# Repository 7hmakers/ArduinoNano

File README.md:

# ArduinoNano
A Development Board based on ATMEGA328P, compatible with Arduino Nano

Made for FZYZ 7HMakers Club

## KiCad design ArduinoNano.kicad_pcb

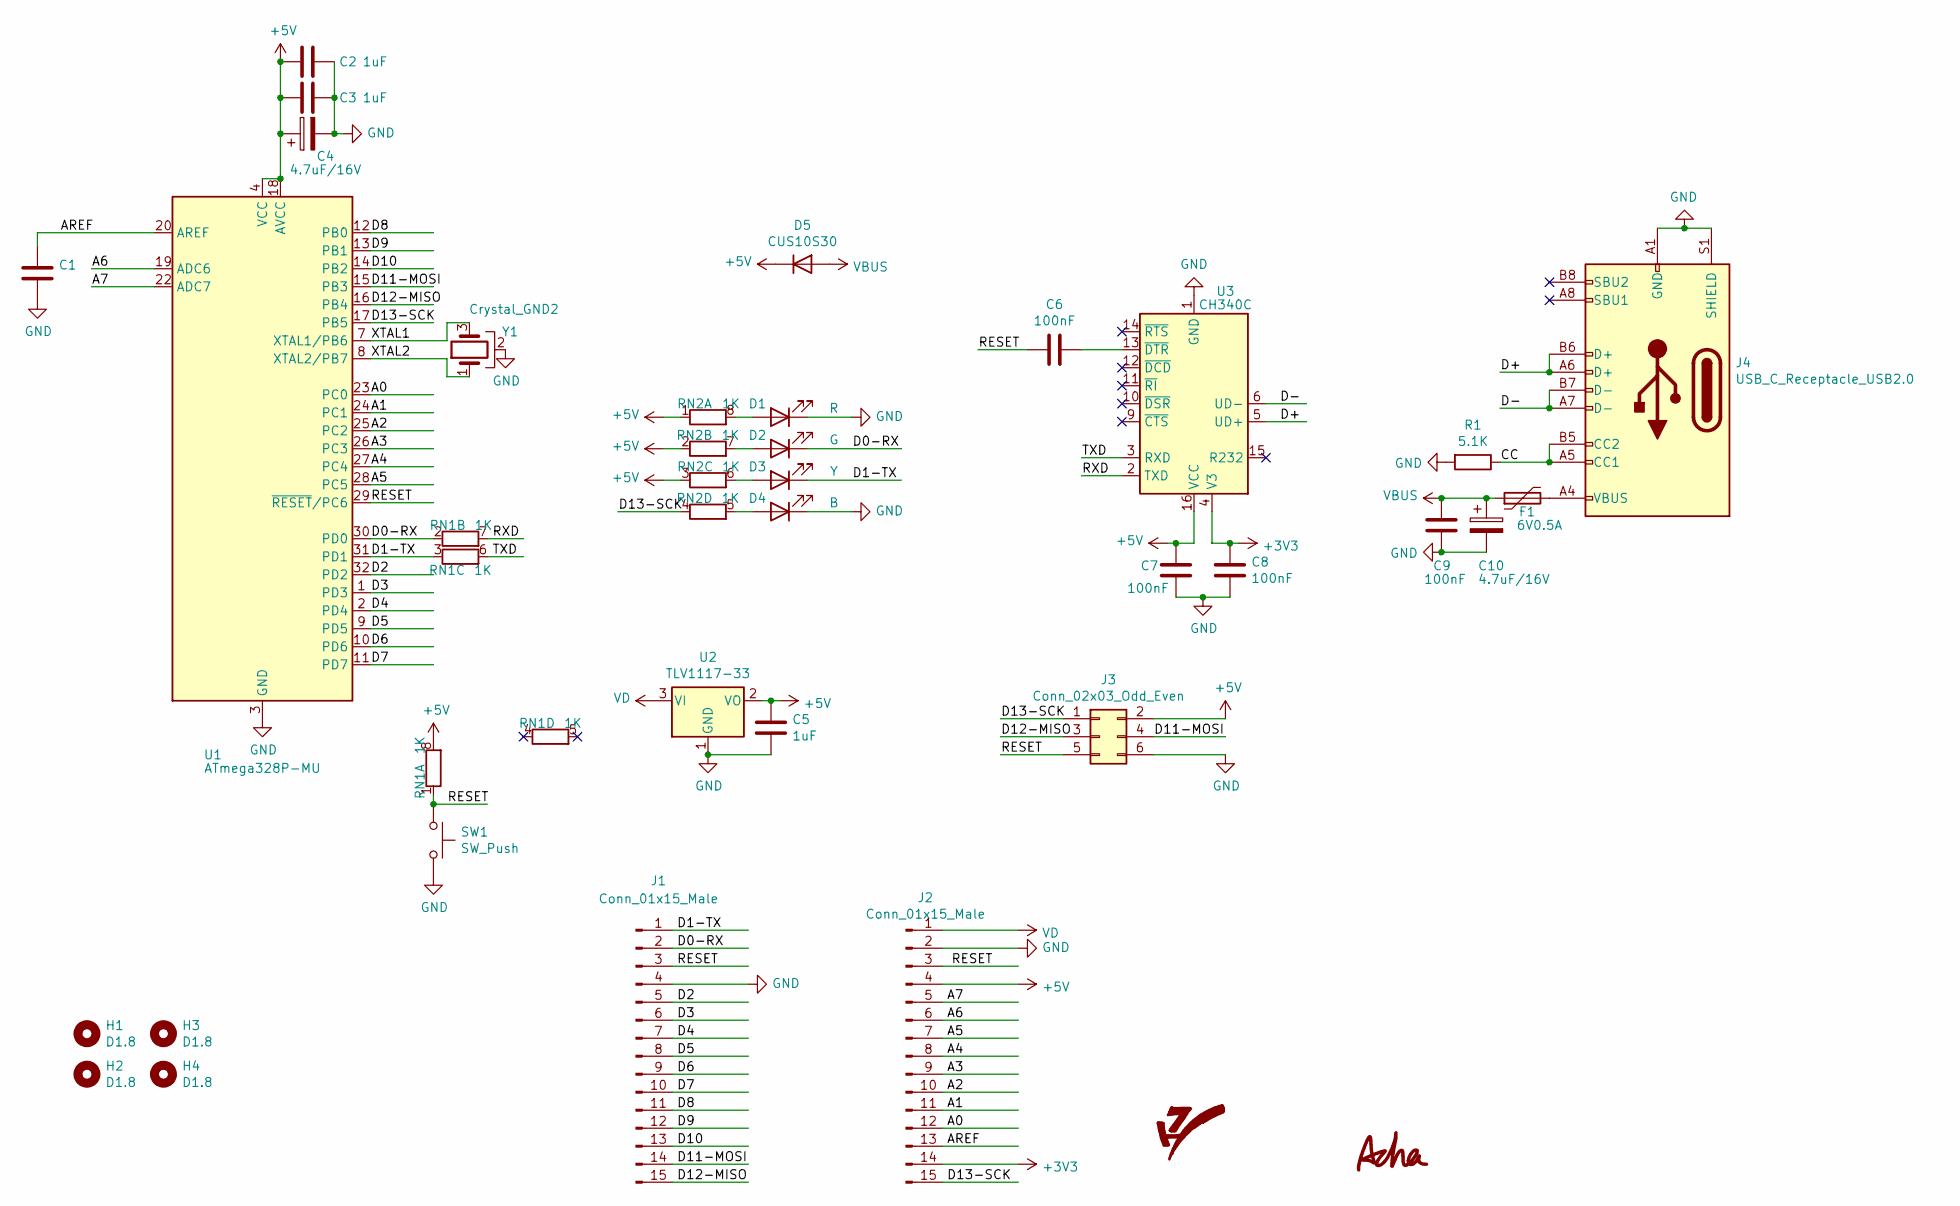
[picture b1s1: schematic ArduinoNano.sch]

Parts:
C1, C6, C7, C8, C9: 100nF; C_0603_1608Metric
C2, C3, C5: 1uF; C_0603_1608Metric
C4, C10: 4.7uF/16V; CP_EIA-3216-18_Kemet-A
D1: R; LED_0603_1608Metric
D2: G; LED_0603_1608Metric
D3: Y; LED_0603_1608Metric
D4: B; LED_0603_1608Metric
D5: CUS10S30; D_SOD-323
F1: 6V0.5A; Fuse_0603_1608Metric
G1: 7Maker_LOGO_SCH_10.8x10.8; 7Maker_LOGO_9.6x9.6
G2: LOGO; Acha_LOGO_5.2x3
H1, H2, H3, H4: D1.8; MountingHole_1.8mm
J1, J2: Conn_01x15_Male; PinHeader_1x15_P2.54mm_Vertical_ard
J3: Conn_02x03_Odd_Even; PinHeader_2x03_P2.54mm_Vertical
J4: USB_C_Receptacle_USB2.0; USB_C_Receptacle_XKB_U262-16XN-4BVC11
R1: 5.1K; R_0603_1608Metric
RN1, RN2: 1K; R_Array_Convex_4x0603
SW1: SW_Push; SW_Push_SPST_NO_Alps_SKRK
U1: ATmega328P-MU; QFN-32-1EP_5x5mm_P0.5mm_EP3.1x3.1mm
U2: TLV1117-33; TLV1117-15CDRJR
U3: CH340C; SOIC-16_3.9x9.9mm_P1.27mm
Y1: Crystal_GND2; Resonator_SMD_muRata_CSTxExxV-3Pin_3.0x1.1mm

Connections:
+3V3: C8.1, J2.14, U3.4 (V3)
+5V: C2.2, C3.2, C4.1, C5.1, C7.1, D5.1 (K), J2.4, J3.2, RN1.8 (R1.2), RN2.1 (R1.1), RN2.2 (R2.1), RN2.3 (R3.1), U1.4 (VCC), U1.6 (VCC), U1.18 (AVCC), U2.2 (VO), U3.16 (VCC)
/A0: J2.12, U1.23 (PC0)
/A1: J2.11, U1.24 (PC1)
/A2: J2.10, U1.25 (PC2)
/A3: J2.9, U1.26 (PC3)
/A4: J2.8, U1.27 (PC4)
/A5: J2.7, U1.28 (PC5)
/A6: J2.6, U1.19 (ADC6)
/A7: J2.5, U1.22 (ADC7)
/AREF: C1.1, J2.13, U1.20 (AREF)
/CC: J4.A5 (CC1), J4.B5 (CC2), R1.1
/D0-RX: D2.1 (K), J1.2, RN1.2 (R2.1), U1.30 (PD0)
/D1-TX: D3.1 (K), J1.1, RN1.3 (R3.1), U1.31 (PD1)
/D2: J1.5, U1.32 (PD2)
/D3: J1.6, U1.1 (PD3)
/D4: J1.7, U1.2 (PD4)
/D5: J1.8, U1.9 (PD5)
/D6: J1.9, U1.10 (PD6)
/D7: J1.10, U1.11 (PD7)
/D8: J1.11, U1.12 (PB0)
/D9: J1.12, U1.13 (PB1)
/D10: J1.13, U1.14 (PB2)
/D11-MOSI: J1.14, J3.4, U1.15 (PB3)
/D12-MISO: J1.15, J3.3, U1.16 (PB4)
/D13-SCK: J2.15, J3.1, RN2.4 (R4.1), U1.17 (PB5)
/D+: J4.A6 (D+), J4.B6 (D+), U3.5 (UD+)
/D-: J4.A7 (D-), J4.B7 (D-), U3.6 (UD-)
/RESET: C6.2, J1.3, J2.3, J3.5, RN1.1 (R1.1), SW1.1, U1.29 (~RESET~/PC6)
/RXD: RN1.7 (R2.2), U3.2 (TXD)
/TXD: RN1.6 (R3.2), U3.3 (RXD)
/XTAL1: U1.7 (XTAL1/PB6), Y1.3
/XTAL2: U1.8 (XTAL2/PB7), Y1.1
GND: C1.2, C2.1, C3.1, C4.2, C5.2, C7.2, C8.2, C9.2, C10.2, D1.1 (K), D4.1 (K), J1.4, J2.2, J3.6, J4.A1 (GND), J4.A12 (GND), J4.B1 (GND), J4.B12 (GND), J4.S1 (SHIELD), R1.2, SW1.2, U1.3 (GND), U1.5 (GND), U1.21 (GND), U1.33 (GND), U2.1 (GND), U3.1 (GND), Y1.2
unnamed: C6.1, U3.13 (~DTR)
unnamed: D1.2 (A), RN2.8 (R1.2)
unnamed: D2.2 (A), RN2.7 (R2.2)
unnamed: D3.2 (A), RN2.6 (R3.2)
unnamed: D4.2 (A), RN2.5 (R4.2)
unnamed: F1.2, J4.A4 (VBUS), J4.A9 (VBUS), J4.B4 (VBUS), J4.B9 (VBUS)
VBUS: C9.1, C10.1, D5.2 (A), F1.1
VD: J2.1, U2.3 (VI)

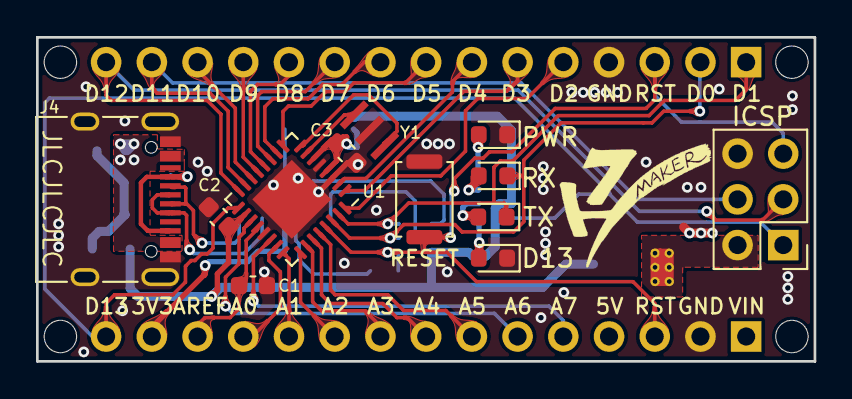
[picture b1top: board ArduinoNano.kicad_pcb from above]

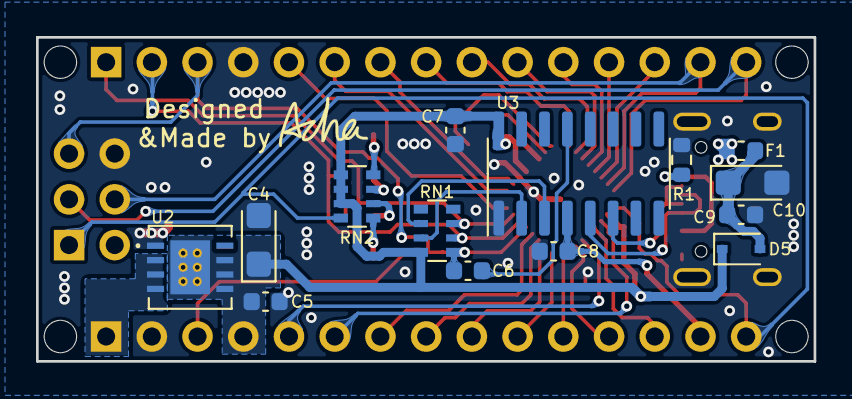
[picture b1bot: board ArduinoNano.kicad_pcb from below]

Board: 2 copper layers, 43.2 x 18.0 mm, 33 parts (15 on the bottom side), 42 nets.

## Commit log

2021-09-21 Sync 2021/09/21 周二 14:00:12.48
